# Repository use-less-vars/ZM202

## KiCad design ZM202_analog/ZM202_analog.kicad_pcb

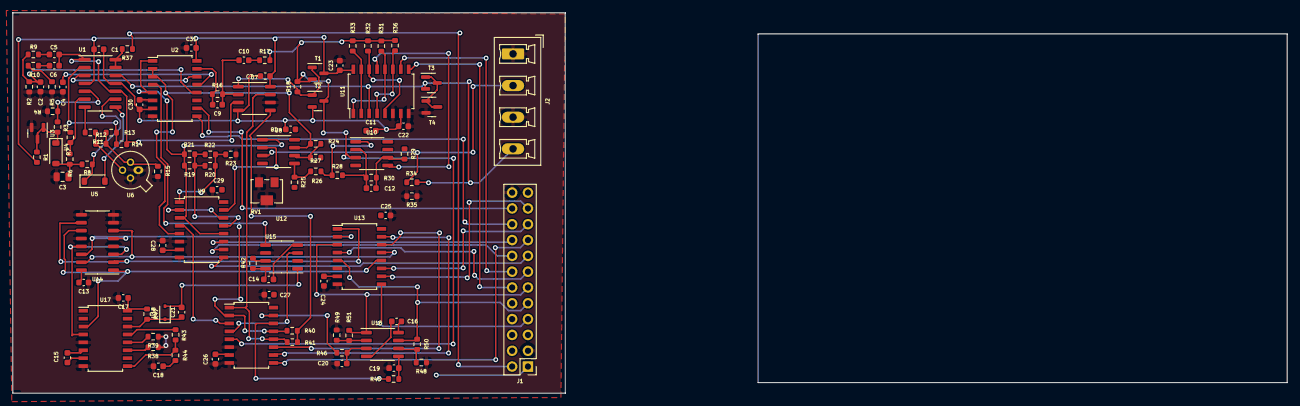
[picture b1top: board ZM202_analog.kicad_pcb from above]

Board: 2 copper layers, 204.7 x 61.1 mm, 107 parts (0 on the bottom side), 89 nets.

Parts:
C1, C7, C8, C11, C13, C14, C16, C17, C18, C22, C23, C24, C25, C26, C27, C28, C29, C30, C31: C0603_100nF_25V; C_0603_1608Metric
C2, C4, C5, C6, C10, C15, C21: C0603_10nF_50V; C_0603_1608Metric
C3: C0805_22uF_6.3V; C_0805_2012Metric
C9: C0603_100pF_50V; C_0603_1608Metric
C12: C0603_82nF_25V; C_0603_1608Metric
C19, C20: C0603_1uF_25V; C_0603_1608Metric
J1: Conn_2x12_2.54_male; PinHeader_2x12_P2.54mm_Vertical
J2: Conn_Screw_1x4_male; PhoenixContact_MCV_1,5_4-G-5.08_1x04_P5.08mm_Vertical
R1, R16, R23, R33, R34, R35: R0603_1k; R_0603_1608Metric
R2, R9, R17: R0603_200k; R_0603_1608Metric
R3, R6, R26, R27, R38, R40, R41, R42, R47, R48, R49: R0603_10k; R_0603_1608Metric
R4, R7, R39: R0603_1M; R_0603_1608Metric
R5, R10, R24: R0603_20k; R_0603_1608Metric
R8: R0603_2.2k; R_0603_1608Metric
R11, R12, R32: R0603_100k; R_0603_1608Metric
R13: R0603_2k; R_0603_1608Metric
R14: R0603_4.75k; R_0603_1608Metric
R15: R0603_750; R_0603_1608Metric
R18: R0603_220; R_0603_1608Metric
R19: R0603_9.09M; R_0603_1608Metric
R20: R0603_909k; R_0603_1608Metric
R21: R0603_90.9k; R_0603_1608Metric
R22: R0603_9.09k; R_0603_1608Metric
R25: R0603_18k; R_0603_1608Metric
R28, R29: R0603_4.99k; R_0603_1608Metric
R30: R0603_2.49k; R_0603_1608Metric
R31: R0603_10M; R_0603_1608Metric
R36: R0603_10; R_0603_1608Metric
R37: R0603_100; R_0603_1608Metric
R43: R0603_330k; R_0603_1608Metric
R44: R0603_22k; R_0603_1608Metric
R45, R46: R0603_470k; R_0603_1608Metric
R50, R51: R0603_15k; R_0603_1608Metric
RV1: R_Potentiometer; Potentiometer_Bourns_3214W_Vertical
T1, T3, T4: BC846BLT1G; SOT-23
T2: BC856B; SOT-23
U1: LM324; SO-14_3.9x8.65mm_P1.27mm
U2, U9, U12, U13, U17: SOIC-16W_5.3x10.2mm_P1.27mm
U3: TL431; SOT-23
U4, U5: 1N4148; D_SOD-123
U6: 2N4416; TO-72-4
U7, U16: LM358B; SO-8_3.9x4.9mm_P1.27mm
U8, U10: TLC2272; SO-8_3.9x4.9mm_P1.27mm
U11: CD4052B; SOIC-16W_5.3x10.2mm_P1.27mm
U14: CD4027; SO-16_3.9x9.9mm_P1.27mm
U15: LM393B; SO-8_3.9x4.9mm_P1.27mm
U18: BZX348; D_SOD-323

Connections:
+5V: C1.2, C7.2, C8.2, C11.2, C13.2, C14.2, C16.2, C17.1, C23.1, C25.2, C27.2, C29.1, C31.2, J1.1, R1.2, R42.2, R47.1, T1.3, U1.4 (+), U2.16 (VDD), U7.8 (+), U8.8 (+), U9.16 (VDD), U10.8 (+), U11.16 (VDD), U12.16 (VDD), U13.16 (VDD), U14.16 (+), U15.8 (+), U16.8 (+), U17.16 (VDD)
-5V: C1.1, C7.1, C8.1, C11.1, C14.1, C16.1, C22.2, C24.1, C26.1, C28.2, C30.1, J1.5, T2.2, U1.11 (-), U2.7 (VEE), U7.4 (-), U8.4 (-), U9.7 (VEE), U10.4 (-), U11.7 (VEE), U12.7 (VEE), U13.7 (VEE), U15.4 (-), U16.4 (-)
/AnalogCore/AVX0: J1.18, U9.11 (A)
/AnalogCore/AVX1: J1.16, U9.10 (B)
/AnalogCore/C/L: J1.20, U2.9 (C)
/AnalogCore/DR+: J2.4, R34.1, T3.2, U1.12 (+), U11.3 (Y)
/AnalogCore/GUARD: J1.2, R37.1
/AnalogCore/IX0: J1.14, U11.10 (A)
/AnalogCore/IX1: J1.12, U11.9 (B)
/AnalogCore/OSC_IN: C5.2, C6.2, R14.2, U1.1, U1.10 (+), U7.3 (+)
/AnalogCore/SN+: J2.2, R34.2, U8.3 (+)
/AnalogCore/VIX: R24.2, U2.2, U2.3, U8.7, U9.5
/AnalogCore/VSRC: J1.22, U2.10 (B)
/AnalogCore/VVX: R19.2, R21.2, U2.1, U2.5, U8.1, U9.3, U9.12
/AnalogCore/VXX: R40.2, U2.4, U12.2, U12.13, U15.5 (+)
/AnalogCore/V_sig: R17.2, R18.2, R31.2, R32.2, R33.2, R36.2, T1.2, T2.3, U10.3 (+), U12.5
/PLL/ADC: J1.13, U13.4
/PLL/CALX: J1.15, U9.9 (C)
/PLL/PHI0: U13.12, U14.1 (Q), U14.11 (K), U17.3 (RefIn)
/PLL/PHI90: U13.13, U14.6 (J), U14.15 (Q)
/PLL/PHI180: U13.1, U14.2 (~Q), U14.10 (J)
/PLL/PHI270: U13.2, U14.5 (K), U14.14 (~Q)
/PLL/PHRZS: J1.19, U13.11 (A)
/PLL/PHSCAL: J1.17, U12.9 (C)
/PLL/PHXZS: J1.21, U13.10 (B)
/PLL/PHX/R: J1.7, U13.9 (C)
/PLL/VR: J1.9, R50.2, U13.5, U16.7
/PLL/VX: J1.11, R51.2, U13.3, U16.1
GND: C2.2, C3.2, C4.2, C13.1, C17.2, C18.2, C19.2, C20.2, C22.1, C23.2, C24.2, C25.1, C26.2, C27.1, C28.1, C29.2, C30.2, C31.1, J1.3, J1.24, J2.1, J2.3, R2.1, R4.2, R5.1, R15.1, R23.1, R35.1, R35.2, R38.1, R39.1, R48.1, R49.1, RV1.2, RV1.3, T4.2, U2.6 (INH), U2.8 (VSS), U3.2 (Ref), U6.1 (S), U6.4, U7.6 (-), U9.6 (INH), U9.8 (VSS), U11.6 (INH), U11.8 (VSS), U12.6 (INH), U12.8 (VSS), U13.6 (INH), U13.8 (VSS), U14.4 (R), U14.7 (S), U14.8 (-), U14.9 (S), U14.12 (R), U15.2 (-), U15.6 (_), U17.5 (Inh), U17.8 (VSS)
unnamed: C2.1, R2.2, R9.2, U2.12
unnamed: C3.1, R6.1, R8.1, U4.2
unnamed: C4.1, R5.2, R10.2, U2.13
unnamed: C5.1, R9.1
unnamed: C6.1, R10.1
unnamed: C9.2, R16.1, U2.15
unnamed: C10.2, R17.1
unnamed: C18.1, R44.1
unnamed: R7.2, R11.1, U1.7
unnamed: R18.1, T1.1, T2.1, U7.1
unnamed: R19.1, R20.2, R21.1, R22.2, U9.13
unnamed: R20.1, R22.1, R23.2, U9.1
unnamed: R25.2, RV1.1
unnamed: R26.2, R28.1, U10.1
unnamed: R27.2, R29.1, U10.7
unnamed: R41.2, U7.7, U12.1, U12.12
unnamed: R42.1, U15.7
unnamed: R45.1, U12.14
unnamed: R46.1, U12.15
unnamed: T3.1, T3.3, T4.1, T4.3
unnamed: U1.8, U5.2
unnamed: U1.3 (+), U2.14
unnamed: R13.2, R14.1, U1.2 (-)
unnamed: R3.1, R4.1, U1.5 (+)
unnamed: R6.2, R7.1, U1.6 (-)
unnamed: R8.2, U1.9 (-), U5.1
unnamed: R37.2, U1.13 (-), U1.14
unnamed: R1.1, R3.2, U3.1 (K), U3.3 (A), U4.1
unnamed: R12.2, R13.1, R15.2, U6.2 (D)
unnamed: R11.2, R12.1, U6.3 (G)
unnamed: C9.1, C10.1, R16.2, U7.2 (-)
unnamed: R40.1, R41.1, U7.5 (+)
unnamed: U8.2 (-), U9.15
unnamed: R25.1, R26.1, U8.5 (+)
unnamed: R24.1, R27.1, U8.6 (-)
unnamed: U9.2, U9.14
unnamed: C12.1, R28.2, R30.2, U10.2 (-)
unnamed: U10.5 (+), U11.13 (X)
unnamed: C12.2, R29.2, R30.1, U10.6 (-)
unnamed: R31.1, U11.1 (Y0), U11.12 (X0)
unnamed: R32.1, U11.5 (Y1), U11.14 (X1)
unnamed: R33.1, U11.2 (Y2), U11.15 (X2)
unnamed: R36.1, U11.4 (Y3), U11.11 (X3)
unnamed: U9.4, U12.3
unnamed: U12.11 (A), U13.14
unnamed: U12.10 (B), U13.15
unnamed: U14.3 (C), U14.13 (C), U17.4 (FOUT)
unnamed: U12.4, U15.3 (+)
unnamed: C20.1, R46.2, U16.3 (+)
unnamed: R49.2, R51.1, U16.2 (-)
unnamed: C19.1, R45.2, U16.5 (+)
unnamed: R48.2, R50.1, U16.6 (-)
unnamed: C15.1, U17.6 (C1)
unnamed: C15.2, U17.7 (C2)
unnamed: R43.2, U17.13 (PC2)
unnamed: R38.2, U17.11 (R1)
unnamed: R39.2, U17.12 (R2)
unnamed: C21.1, R47.2, U17.14 (SigIn), U18.1 (K)
unnamed: R43.1, R44.2, U17.9 (VCOin)
unnamed: C21.2, U15.1, U18.2 (A)

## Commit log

2023-05-13 Added project-, schematic- and pcb-files.
2023-05-13 Added a few example wires.
2023-06-29 put parts into oscillator sheet
2023-06-29 Oscillator is wired.
2023-06-30 Started with the analog part, placing the symbols.
2023-06-30 Forgot to commit the analog_core-file.
2023-06-30 Wired analog part.
2023-07-01 Started placing symbols for the PLL-part.
2023-07-01 Added PLL-circuit and added labels.
2023-07-01 Added labels and connections to outside-world.
2023-07-03 Labels everywhere and connected hierarchical sheets.
2023-07-04 Connected hierarchical outlets to connector.
2023-07-04 Changed amplification resistor/cap in the analog core to 82nF/2.49k and did some various changes in the symbols and updated them into the schematic. Added PWR-flags
2023-07-09 Added 4-Pin connector for DUT
2023-10-07 Finished first version of PCB. Added some capacitors at digital ICs.
2023-10-07 Changed board size.
2023-10-07 Minor changes, fixed gnd-island.
2023-10-19 Outline of Raspberry-Pi added.
2023-10-23 New part placement.
2023-10-25 2-Layer design with 5V connections missing.
